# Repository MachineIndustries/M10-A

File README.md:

# M10-A
Design files for the the M10-A 10 key macropad, created in collaboration with Ramaworks.

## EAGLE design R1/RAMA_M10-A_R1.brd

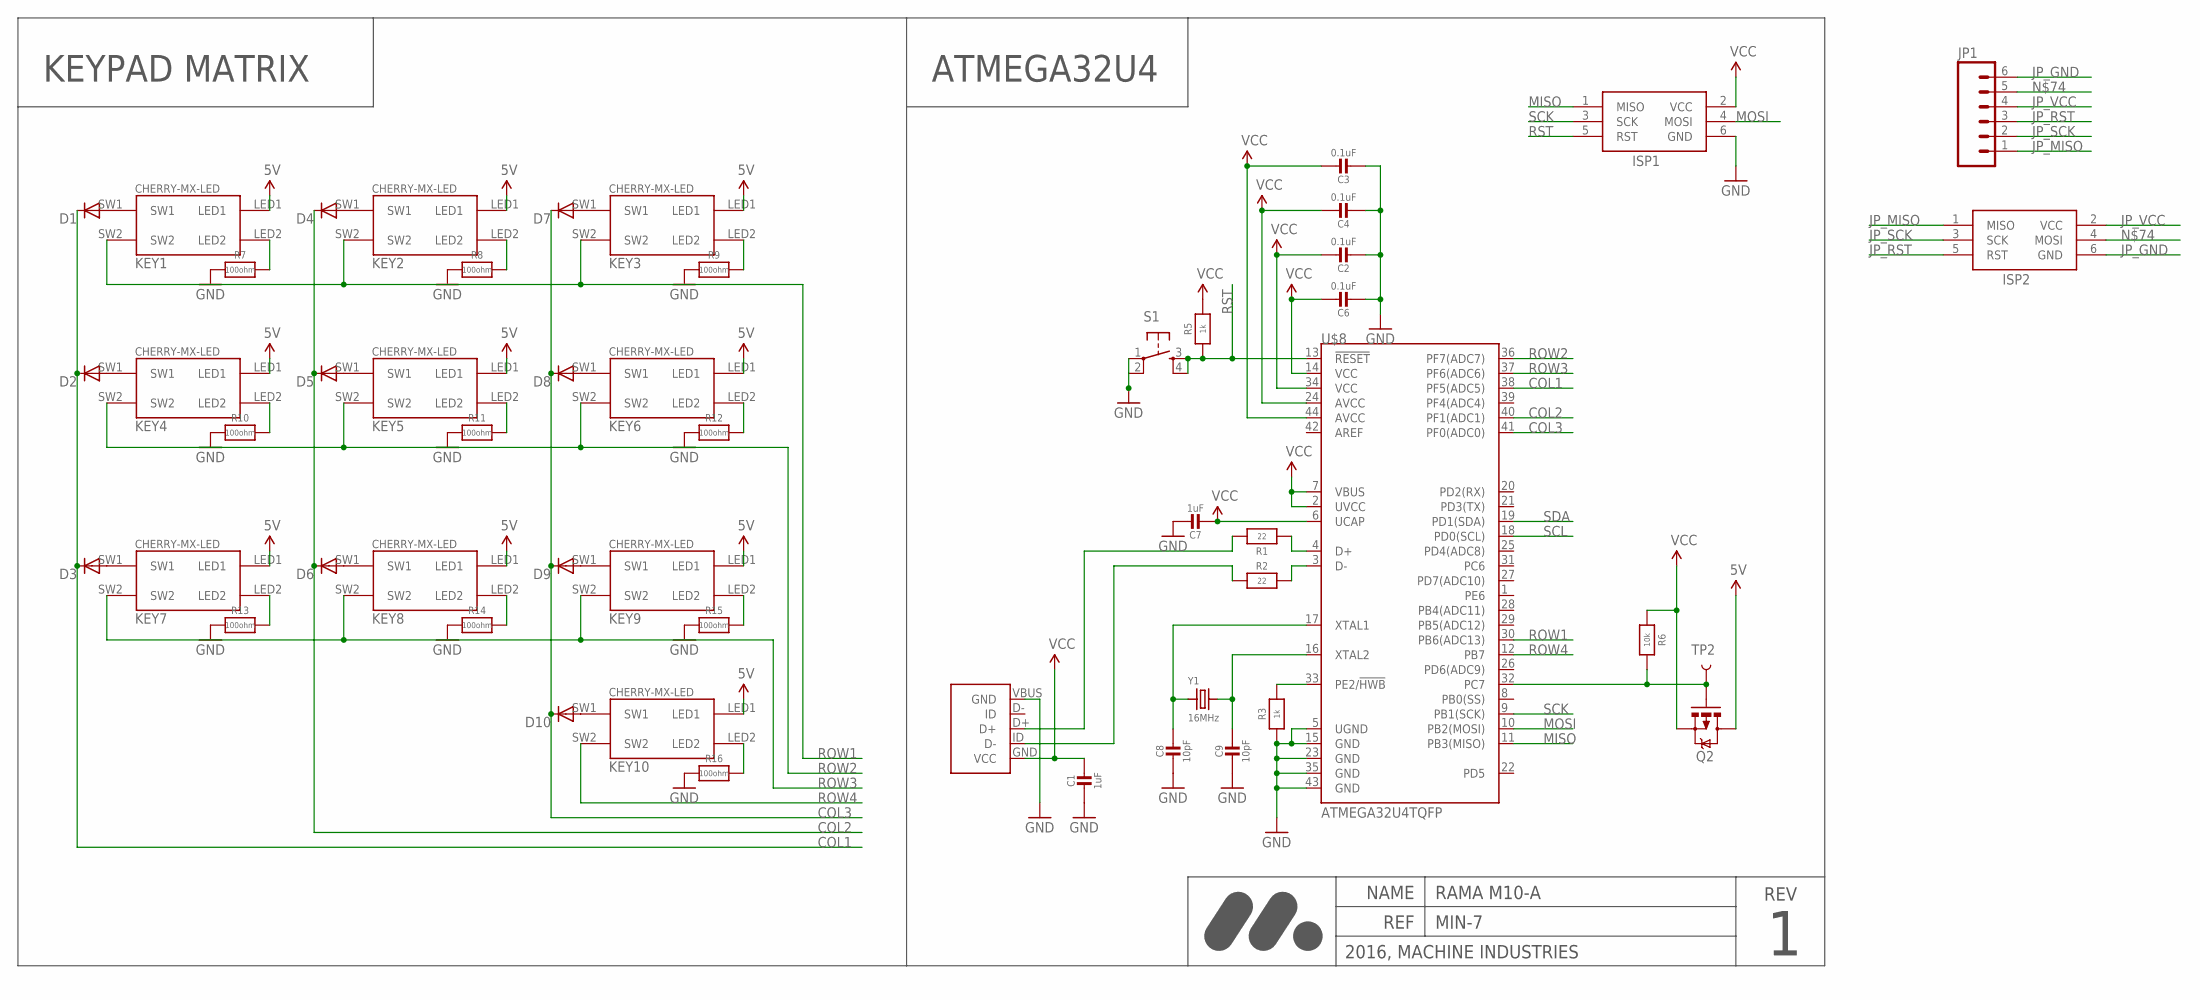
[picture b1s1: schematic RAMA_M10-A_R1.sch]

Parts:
C1, C7: 1uF; _0603MP
C2, C3, C4, C6: 0.1uF; _0603MP
C8, C9: 10pF; _0603MP
D1, D2, D3, D4, D5, D6, D7, D8, D9, D10: DIODESOD; SOD-323
ISP1, ISP2: AVRISP-SMT
JP1: M06SIP; 1X06
KEY1, KEY2, KEY3, KEY4, KEY5, KEY6, KEY7, KEY8, KEY9, KEY10: CHERRY-MX-LED-18X18
Q2: PCHANNEL-MOSFET; SOT23-3
R1, R2: 22; _0603MP
R3, R5: 1k; _0603MP
R6: 10k; _0603MP
R7, R8, R9, R10, R11, R12, R13, R14, R15, R16: 100ohm; _0603MP
S1: TAC_SWITCHSMD; TACTILE_SWITCH_SMD
TP2: TEST-POINT3; PAD.03X.03
U$8: ATMEGA32U4TQFP; SPARKFUN-DIGITALIC_TQFP44
U$9: MICRO-USB-B-FEMALE; 10118192-0001LF
Y1: 16MHz; CRYSTAL_3.2X2.5

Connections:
5V: KEY1.LED1, KEY2.LED1, KEY3.LED1, KEY4.LED1, KEY5.LED1, KEY6.LED1, KEY7.LED1, KEY8.LED1, KEY9.LED1, KEY10.LED1, Q2.3 (D)
COL1: D1.1 (C), D2.1 (C), D3.1 (C), U$8.38 (PF5(ADC5))
COL2: D4.1 (C), D5.1 (C), D6.1 (C), U$8.40 (PF1(ADC1))
COL3: D7.1 (C), D8.1 (C), D9.1 (C), D10.1 (C), U$8.41 (PF0(ADC0))
GND: C1.2, C2.2, C3.2, C4.2, C6.2, C7.1, C8.2, C9.2, ISP1.6 (GND), R3.1, R7.1, R8.1, R9.1, R10.1, R11.1, R12.1, R13.1, R14.1, R15.1, R16.1, S1.1, S1.2, U$8.5 (UGND), U$8.15 (GND), U$8.23 (GND), U$8.35 (GND), U$8.43 (GND), U$9.VBUS (GND)
JP_GND: ISP2.6 (GND), JP1.6
JP_MISO: ISP2.1 (MISO), JP1.1
JP_RST: ISP2.5 (RST), JP1.3
JP_SCK: ISP2.3 (SCK), JP1.2
JP_VCC: ISP2.2 (VCC), JP1.4
MISO: ISP1.1 (MISO), U$8.11 (PB3(MISO))
MOSI: ISP1.4 (MOSI), U$8.10 (PB2(MOSI))
unnamed: R1.1, U$9.D+
unnamed: R2.1, U$9.ID (D-)
unnamed: R2.2, U$8.3 (D-)
unnamed: R1.2, U$8.4 (D+)
unnamed: C8.1, U$8.17 (XTAL1), Y1.1
unnamed: C9.1, U$8.16 (XTAL2), Y1.2
unnamed: R3.2, U$8.33 (PE2/!HWB)
unnamed: Q2.1 (G), R6.2, TP2.P$1, U$8.32 (PC7)
unnamed: D1.2 (A), KEY1.SW1
unnamed: D2.2 (A), KEY4.SW1
unnamed: D3.2 (A), KEY7.SW1
unnamed: D4.2 (A), KEY2.SW1
unnamed: D5.2 (A), KEY5.SW1
unnamed: D6.2 (A), KEY8.SW1
unnamed: D9.2 (A), KEY9.SW1
unnamed: D8.2 (A), KEY6.SW1
unnamed: D7.2 (A), KEY3.SW1
unnamed: D10.2 (A), KEY10.SW1
unnamed: KEY7.LED2, R13.2
unnamed: KEY8.LED2, R14.2
unnamed: KEY9.LED2, R15.2
unnamed: KEY10.LED2, R16.2
unnamed: KEY4.LED2, R10.2
unnamed: KEY5.LED2, R11.2
unnamed: KEY6.LED2, R12.2
unnamed: KEY3.LED2, R9.2
unnamed: KEY2.LED2, R8.2
unnamed: KEY1.LED2, R7.2
unnamed: ISP2.4 (MOSI), JP1.5
ROW1: KEY1.SW2, KEY2.SW2, KEY3.SW2, U$8.30 (PB6(ADC13))
ROW2: KEY4.SW2, KEY5.SW2, KEY6.SW2, U$8.36 (PF7(ADC7))
ROW3: KEY7.SW2, KEY8.SW2, KEY9.SW2, U$8.37 (PF6(ADC6))
ROW4: KEY10.SW2, U$8.12 (PB7)
RST: ISP1.5 (RST), R5.1, S1.3, S1.4, U$8.13 (!RESET)
SCK: ISP1.3 (SCK), U$8.9 (PB1(SCK))
SCL: U$8.18 (PD0(SCL))
SDA: U$8.19 (PD1(SDA))
VCC: C1.1, C2.1, C3.1, C4.1, C6.1, C7.2, ISP1.2 (VCC), Q2.2 (S), R5.2, R6.1, U$8.2 (UVCC), U$8.6 (UCAP), U$8.7 (VBUS), U$8.14 (VCC), U$8.24 (AVCC), U$8.34 (VCC), U$8.44 (AVCC), U$9.GND (VCC)

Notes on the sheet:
KEYPAD MATRIX
REV
NAME
REF
2016, MACHINE INDUSTRIES
MIN-7
RAMA M10-A
ATMEGA32U4

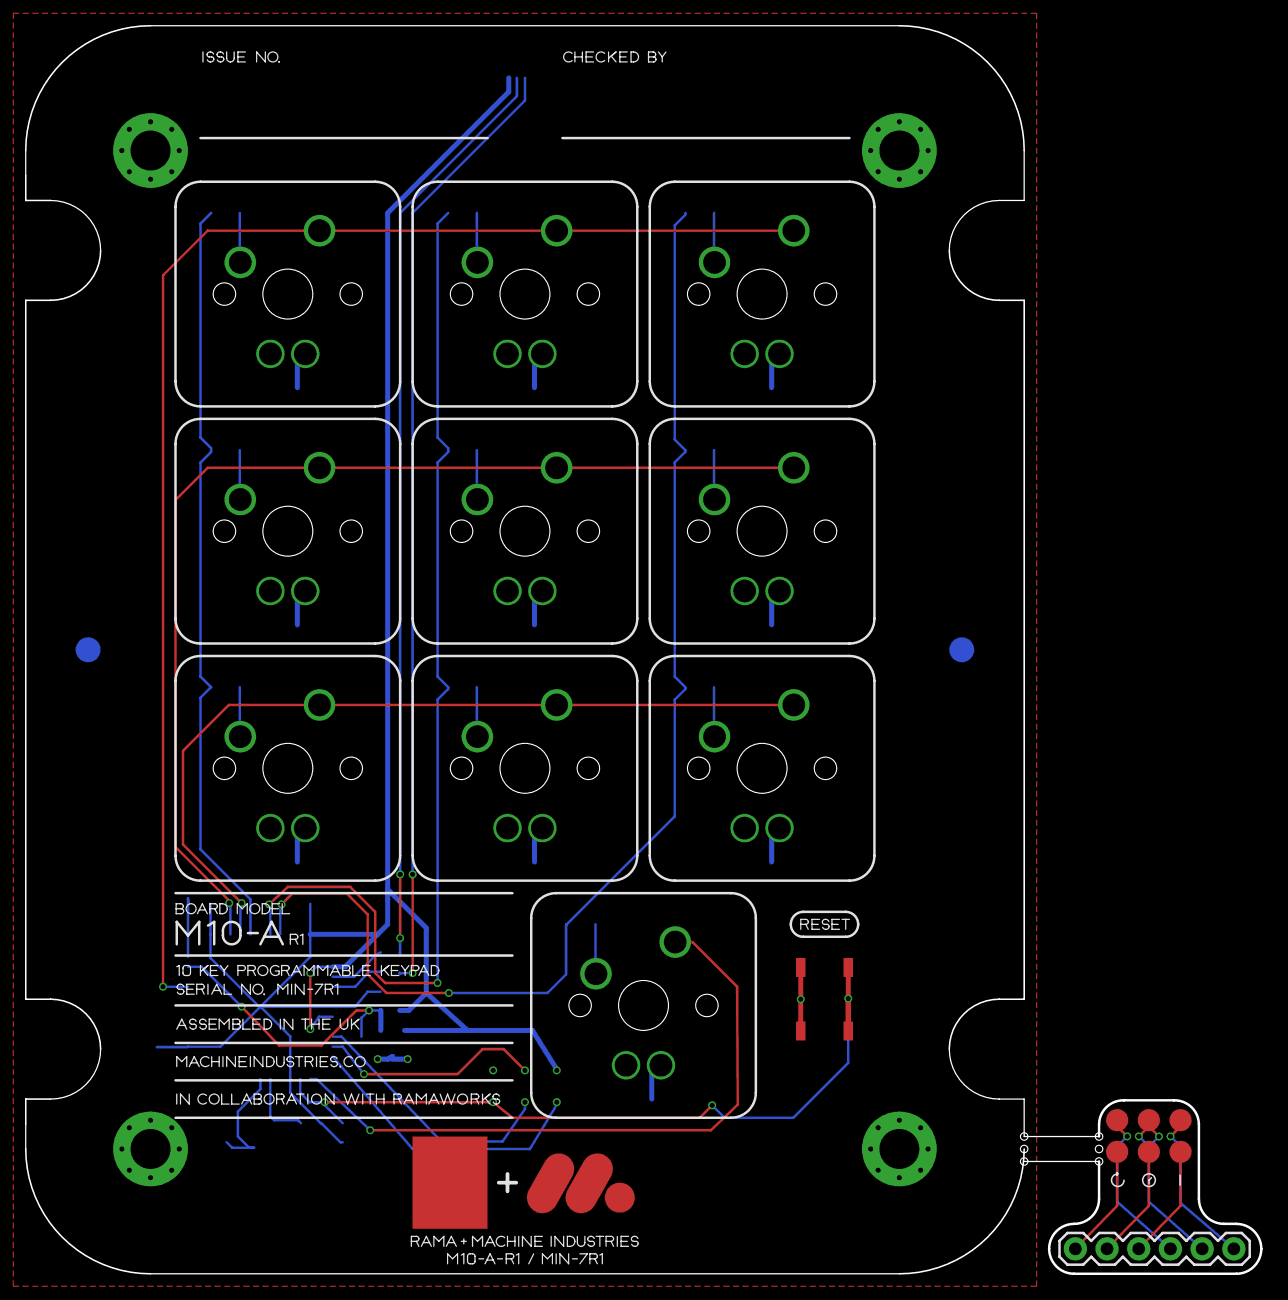
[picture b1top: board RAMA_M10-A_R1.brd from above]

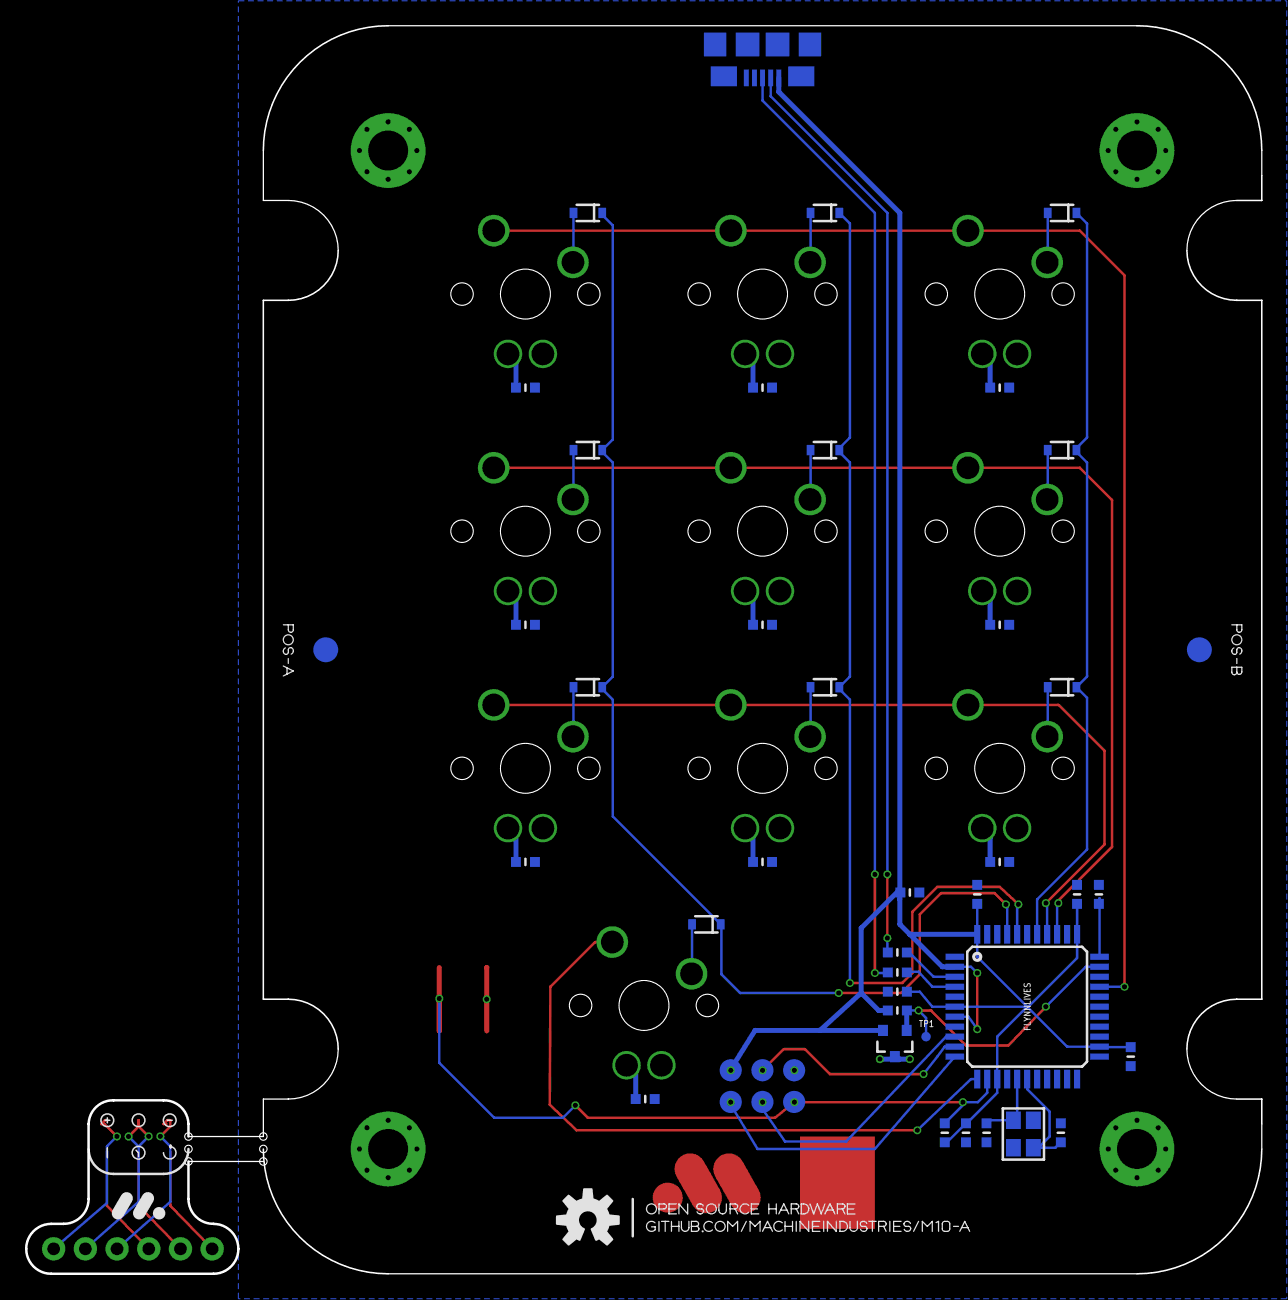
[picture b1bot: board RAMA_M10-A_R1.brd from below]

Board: 2 copper layers, 99.0 x 100.0 mm, 52 parts (39 on the bottom side), 48 nets.

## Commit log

2016-03-12 Minor silkscreen tweaks for production with DirtyPCBS.com
2016-03-12 Neatening up schematic
2016-03-22 Modified mounting holes, added dimension routing for enclosure bosses
2016-03-26 Rounded corners, strengthened mounting holes, changed fonts to nicer hand-drawn font, altered USB & TQFN-44 footprints, fixed incorrectly reversed MISO/MOSI, altered copper pour on RAMA & Machine log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
2016-07-11 Pre-prod

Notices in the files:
parts and their libraries:
SparkFun-DigitalIC: Licensing: Creative Commons ShareAlike 4.0 International - https://creativecommons.org/licenses/by-sa/4.0
